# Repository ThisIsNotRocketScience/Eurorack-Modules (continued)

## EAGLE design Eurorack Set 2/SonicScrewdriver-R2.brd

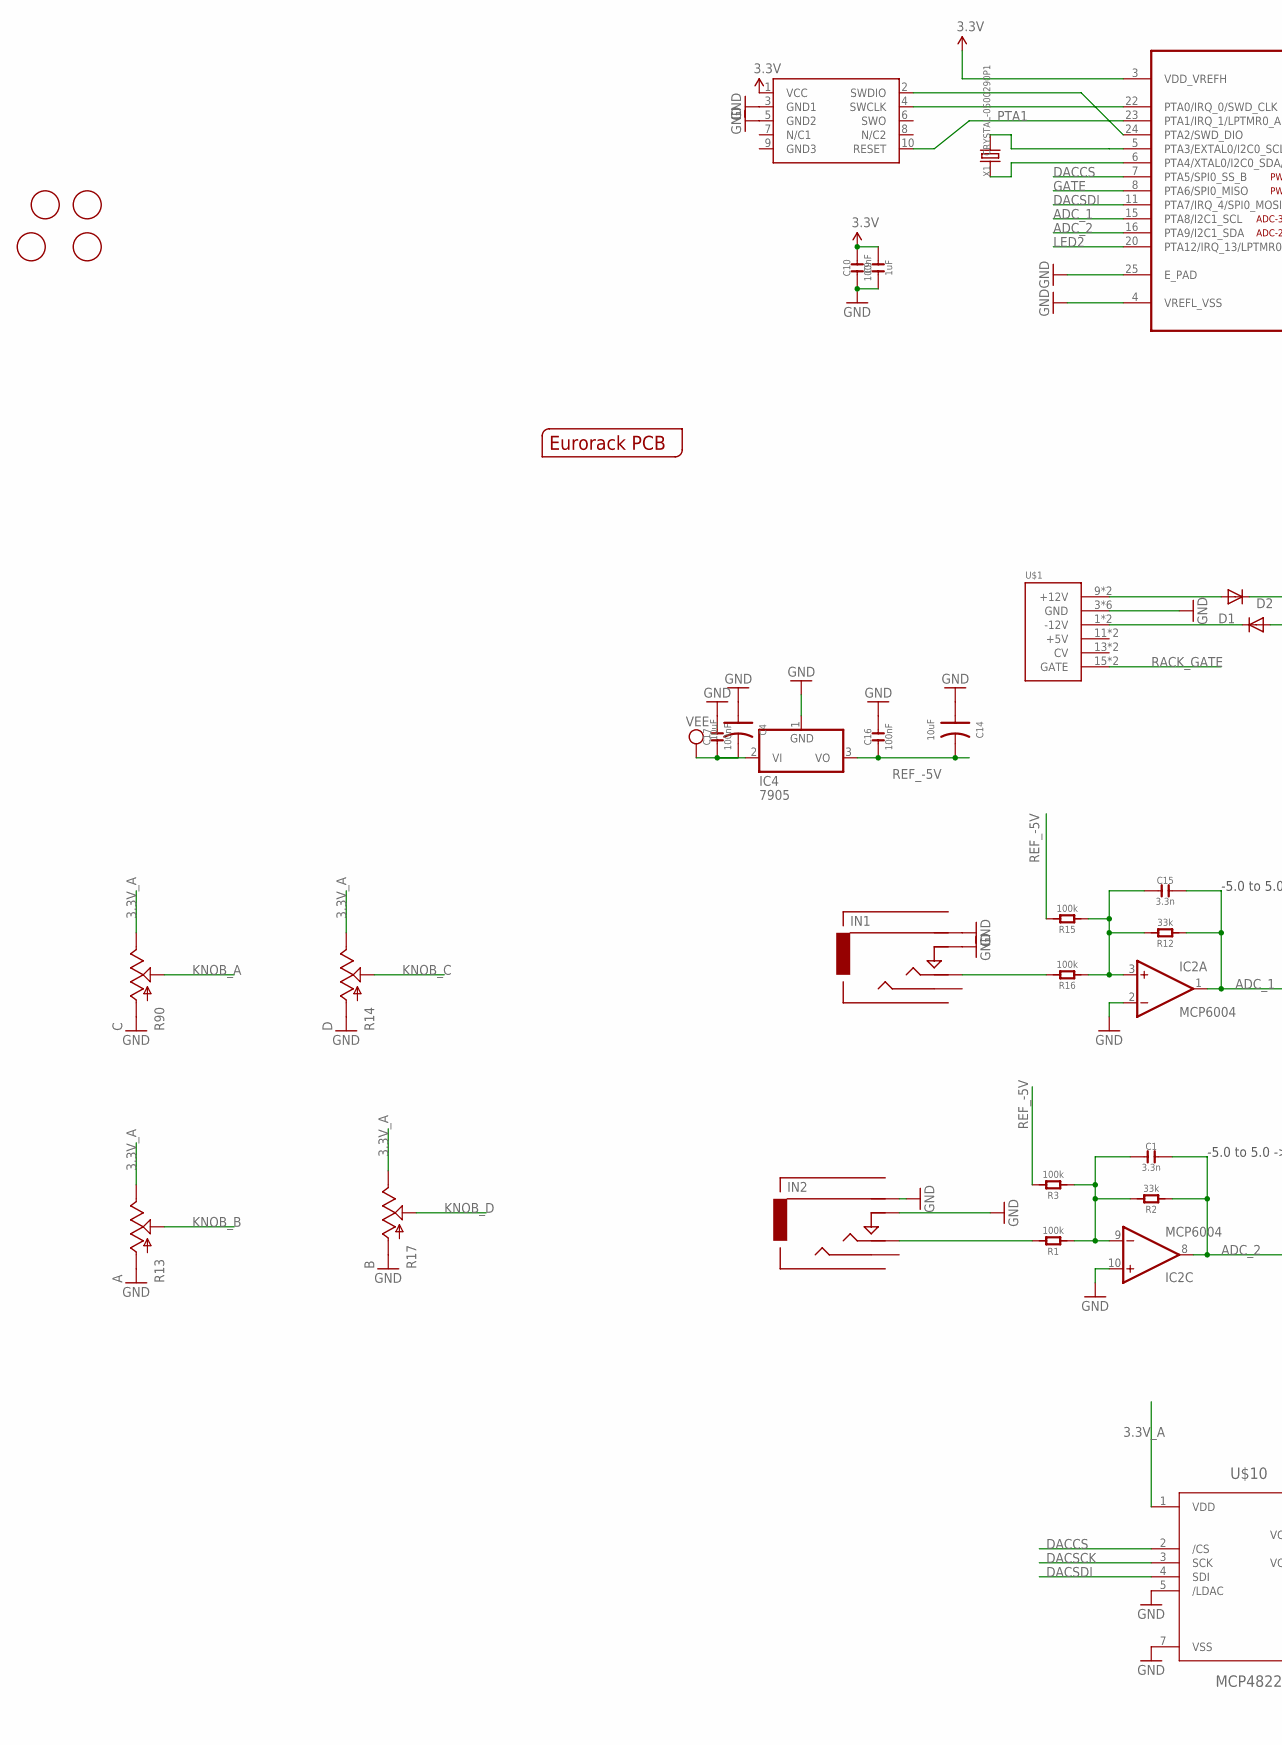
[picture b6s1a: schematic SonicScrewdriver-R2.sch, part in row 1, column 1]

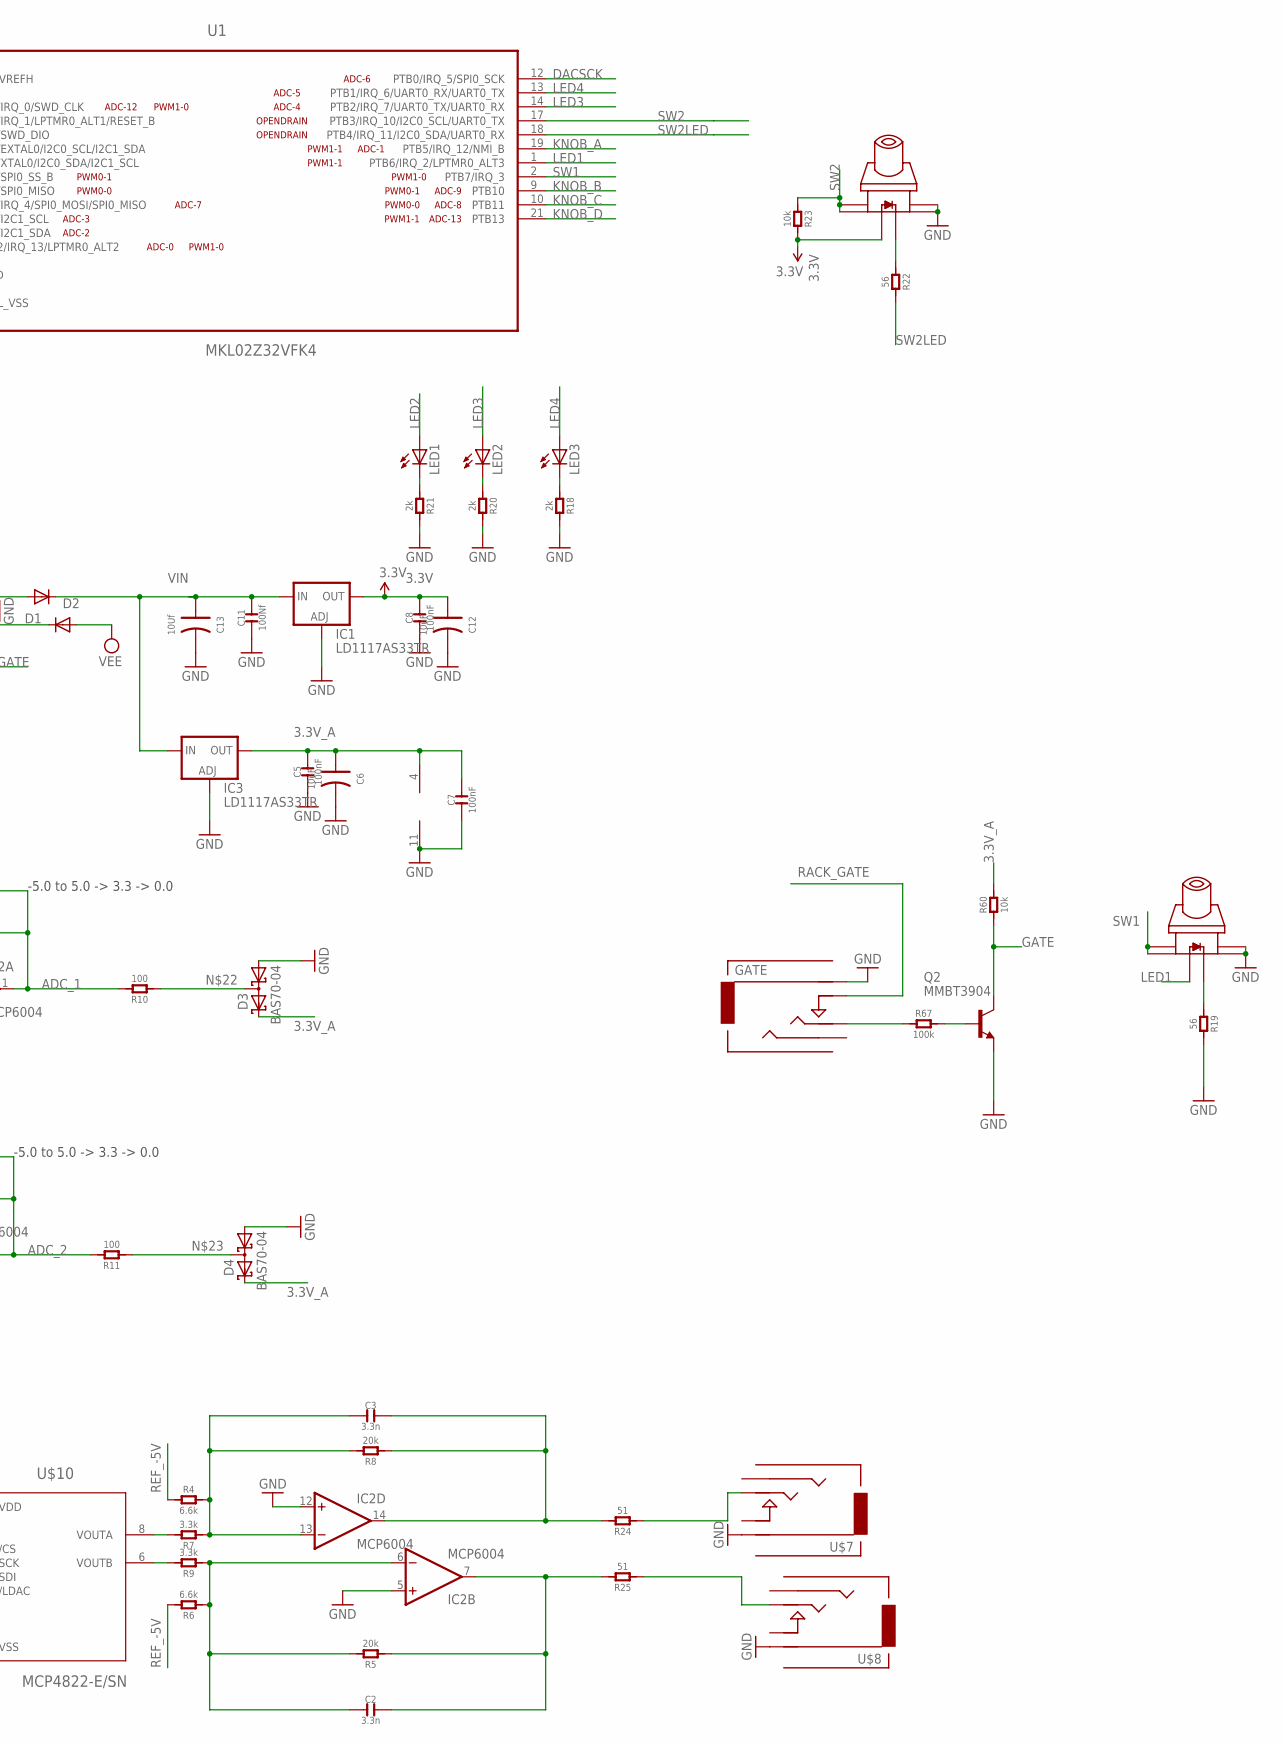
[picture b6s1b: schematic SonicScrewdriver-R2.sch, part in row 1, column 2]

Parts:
C1, C2, C3, C15: 3.3n; C0603
C4, C6, C12, C14: 10uF; AVX-A
C5, C7, C8, C10, C16, C17: 100nF; C0603
C9: 1uF; C0603
C11: 100Nf; C0603
C13: 10Uf; AVX-A
D1, D2: 1N5819HW; SOD123
D3, D4: BAS70-04; SOT23
GATE: Gate; 3.5MM-JACK-SWITCH-13MM-INPUT
IC1, IC3: LD1117AS33TR; SOT223
IC2: MCP6004; SO14
IC4: 7905; TO220H
IN1: In 2; 3.5MM-JACK-SWITCH-13MM-INPUT
IN2: In 1; 3.5MM-JACK-SWITCH-13MM-INPUT
LED1, LED2, LED3: LED3MM
Q2: MMBT3904; SOT23-BEC
R1, R3, R15, R16, R67: 100k; R0603
R2, R12: 33k; R0603
R4, R6: 6.6k; R0603
R5, R8: 20k; R0603
R7, R9: 3.3k; R0603
R10, R11: 100; R0603
R13: A; OG-POTS_ALPS_POT_VERTICAL
R14: D; OG-POTS_ALPS_POT_VERTICAL
R17: B; OG-POTS_ALPS_POT_VERTICAL
R18, R20, R21: 2k; R0603
R19, R22: 56; R0603
R23, R60: 10k; R0603
R24, R25: 51; R0603
R90: C; OG-POTS_ALPS_POT_VERTICAL
SWD1: CORTEX_SWD; M50-3600542
U1: MKL02Z32VFK4; QFN50P400X400X100-25N
U$1: POWER; POWER_16
U$2: EURORACK_PCB8HP; EURORACK8HPPCB
U$3, U$6: SWITCH_W_LED_PB6149L-X-102WHITE; PB6149L
U$4, U$5, U$9, U$11: FIDUCIAL; FIDUCIAL_1MM
U$7: Out 2; 3.5MM-JACK-SWITCH-13MM-OUTPUT
U$8: Out 1; 3.5MM-JACK-SWITCH-13MM-OUTPUT
U$10: MCP4822-E/SN; SOIC8-N_MC
X1: CRYSTAL-0500290P1; 2P-SMD-5.0X3.2

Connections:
3.3V: C8.2, C9.2, C10.2, C12.+ (1), IC1.2 (OUT), IC1.4 (OUT), R23.2, SWD1.1 (VCC), U1.3 (VDD_VREFH), U$3.LEDPOS (POS)
3.3V_A: C5.2, C6.+ (1), C7.2, D3.2 (C2), D4.2 (C2), IC2.4 (V+), IC3.2 (OUT), IC3.4 (OUT), R13.P$1 (E), R14.P$1 (E), R17.P$1 (E), R60.2, R90.P$1 (E), U$10.1 (VDD)
ADC_1: C15.2, IC2.1 (OUT), R10.2, R12.1, U1.15 (PTA8/I2C1_SCL)
ADC_2: C1.2, IC2.8 (OUT), R2.1, R11.2, U1.16 (PTA9/I2C1_SDA)
DACCS: U1.7 (PTA5/SPI0_SS_B), U$10.2 (/CS)
DACSCK: U1.12 (PTB0/IRQ_5/SPI0_SCK), U$10.3 (SCK)
DACSDI: U1.11 (PTA7/IRQ_4/SPI0_MOSI/SPI0_MISO), U$10.4 (SDI)
GATE: Q2.C, R60.1, U1.8 (PTA6/SPI0_MISO)
GND: C4.+ (1), C5.1, C6.- (2), C7.1, C8.1, C9.1, C10.1, C11.1, C12.- (2), C13.- (2), C14.+ (1), C16.2, C17.2, D3.1 (A1), D4.1 (A1), GATE.RING@1 (RING), GATE.RING@2 (RING), IC1.1 (ADJ), IC2.2 (-IN), IC2.5 (+IN), IC2.10 (+IN), IC2.11 (V-), IC2.12 (+IN), IC3.1 (ADJ), IC4.1 (GND), IN1.RING@1 (RING), IN1.RING@2 (RING), IN1.SWITCH@1 (SWITCH), IN1.SWITCH@2 (SWITCH), IN2.RING@1 (RING), IN2.RING@2 (RING), IN2.SWITCH@1 (SWITCH), IN2.SWITCH@2 (SWITCH), Q2.E, R13.P$3 (A), R14.P$3 (A), R17.P$3 (A), R18.2, R19.2, R20.2, R21.2, R90.P$3 (A), SWD1.3 (GND1), SWD1.5 (GND2), U1.4 (VREFL_VSS), U1.25 (E_PAD), U$1.3 (GND), U$1.4 (GND), U$1.5 (GND), U$1.6 (GND), U$1.7 (GND), U$1.8 (GND), U$3.3, U$3.4, U$6.3, U$6.4, U$7.RING@1 (RING), U$7.RING@2 (RING), U$8.RING@1 (RING), U$8.RING@2 (RING), U$10.5 (/LDAC), U$10.7 (VSS)
KNOB_A: R90.P$2 (S), U1.19 (PTB5/IRQ_12/NMI_B)
KNOB_B: R13.P$2 (S), U1.9 (PTB10)
KNOB_C: R14.P$2 (S), U1.10 (PTB11)
KNOB_D: R17.P$2 (S), U1.21 (PTB13)
LED1: U1.1 (PTB6/IRQ_2/LPTMR0_ALT3), U$6.LEDPOS (POS)
LED2: LED1.A, U1.20 (PTA12/IRQ_13/LPTMR0_ALT2)
LED3: LED2.A, U1.14 (PTB2/IRQ_7/UART0_TX/UART0_RX)
LED4: LED3.A, U1.13 (PTB1/IRQ_6/UART0_RX/UART0_TX)
unnamed: U1.5 (PTA3/EXTAL0/I2C0_SCL/I2C1_SDA), X1.2
unnamed: U1.6 (PTA4/XTAL0/I2C0_SDA/I2C1_SCL), X1.1
unnamed: IN1.TIP@1 (TIP), IN1.TIP@2 (TIP), R16.2
unnamed: C15.1, IC2.3 (+IN), R12.2, R15.1, R16.1
unnamed: SWD1.4 (SWCLK), U1.22 (PTA0/IRQ_0/SWD_CLK)
unnamed: IN2.TIP@1 (TIP), IN2.TIP@2 (TIP), R1.2
unnamed: SWD1.2 (SWDIO), U1.24 (PTA2/SWD_DIO)
unnamed: C1.1, IC2.9 (-IN), R1.1, R2.2, R3.1
unnamed: C2.1, IC2.6 (-IN), R5.2, R6.1, R9.1
unnamed: C3.1, IC2.13 (-IN), R4.2, R7.1, R8.2
unnamed: R7.2, U$10.8 (VOUTA)
unnamed: R9.2, U$10.6 (VOUTB)
unnamed: D1.A, U$1.9 (+12V), U$1.10 (+12V)
unnamed: R19.1, U$6.LEDNEG (NEG)
unnamed: LED3.K (C), R18.1
unnamed: LED2.K (C), R20.1
unnamed: LED1.K (C), R21.1
unnamed: C3.2, IC2.14 (OUT), R8.1, R24.2
unnamed: R22.1, U$3.LEDNEG (NEG)
unnamed: R25.1, U$8.TIP@1 (TIP), U$8.TIP@2 (TIP)
unnamed: R24.1, U$7.TIP@1 (TIP), U$7.TIP@2 (TIP)
unnamed: D3.3 (C1A2), R10.1
unnamed: D4.3 (C1A2), R11.1
unnamed: C2.2, IC2.7 (OUT), R5.1, R25.2
unnamed: GATE.TIP@1 (TIP), GATE.TIP@2 (TIP), R67.1
unnamed: D2.C, U$1.1 (-12V), U$1.2 (-12V)
unnamed: Q2.B, R67.2
PTA1: SWD1.10 (RESET), U1.23 (PTA1/IRQ_1/LPTMR0_ALT1/RESET_B)
RACK_GATE: GATE.SWITCH@1 (SWITCH), GATE.SWITCH@2 (SWITCH), U$1.15 (GATE), U$1.16 (GATE)
REF_-5V: C14.- (2), C16.1, IC4.3 (VO), R3.2, R4.1, R6.2, R15.2
SW1: U1.2 (PTB7/IRQ_3), U$6.1, U$6.2
SW2: R23.1, U1.17 (PTB3/IRQ_10/I2C0_SCL/UART0_TX), U$3.1, U$3.2
SW2LED: R22.2, U1.18 (PTB4/IRQ_11/I2C0_SDA/UART0_RX)
VEE: C4.- (2), C17.1, D2.A, IC4.2 (VI)
VIN: C11.2, C13.+ (1), D1.C, IC1.3 (IN), IC3.3 (IN)

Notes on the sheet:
-5.0 to 5.0 -> 3.3 -> 0.0

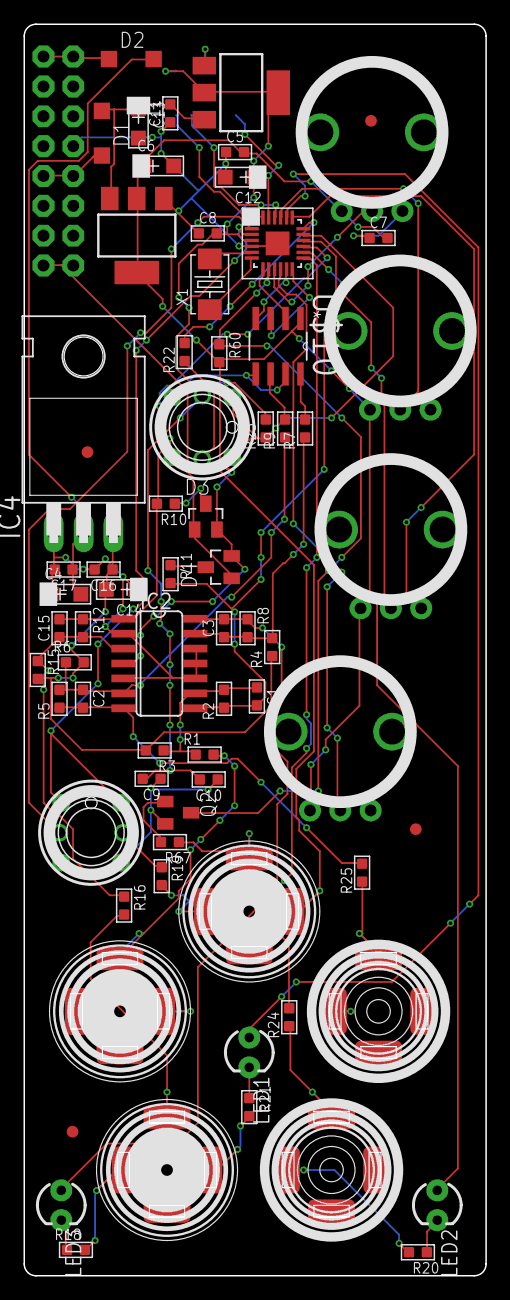
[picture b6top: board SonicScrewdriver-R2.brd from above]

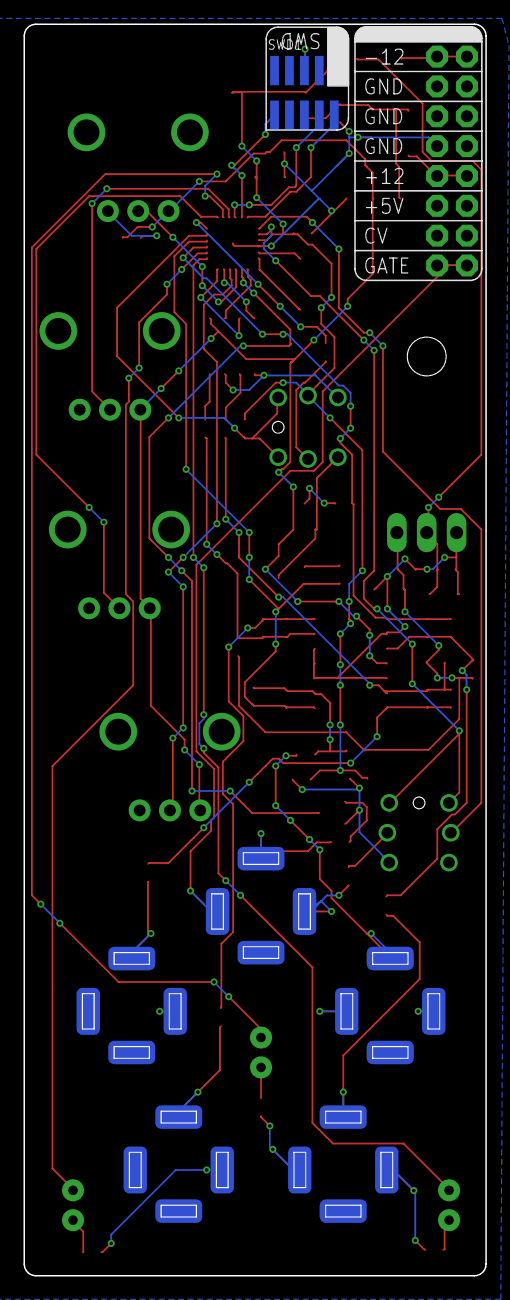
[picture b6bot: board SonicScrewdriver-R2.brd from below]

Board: 2 copper layers, 39.3 x 106.5 mm, 74 parts (2 on the bottom side), 52 nets.

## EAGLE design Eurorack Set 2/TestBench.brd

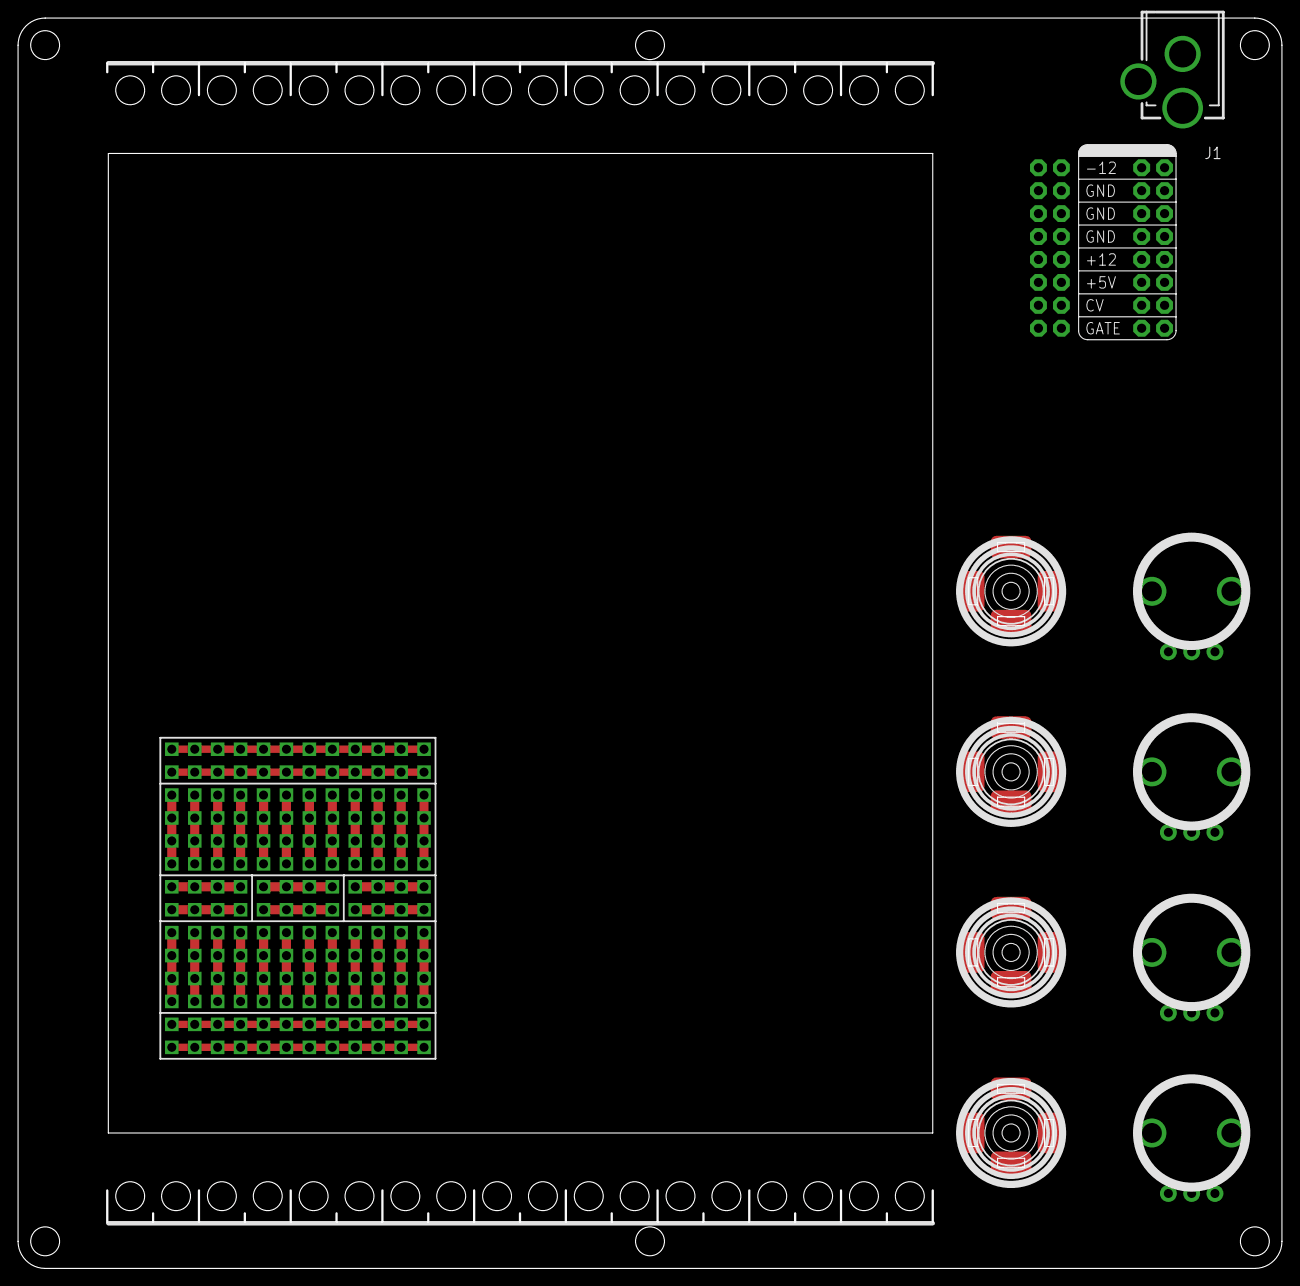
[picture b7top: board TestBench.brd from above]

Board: 2 copper layers, 140.0 x 138.5 mm, 12 parts (1 on the bottom side), 6 nets, no tracks yet.

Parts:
J1: DC_BARREL_JACK_PTH_2MM
U$1, U$2: POWER; POWER_16
U$3: PROTOAREA; PROTO_10_24
U$4, U$5, U$6, U$7: OG-POTS_ALPS_POT_VERTICAL
U$8, U$9, U$10, U$11: AUDIO-JACKOUTPUT; 3.5MM-JACK-SWITCH-13MM-OUTPUT

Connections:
unnamed: U$1.9, U$1.10, U$2.9, U$2.10
unnamed: U$1.3, U$1.4, U$1.5, U$1.6, U$1.7, U$1.8, U$2.3, U$2.4, U$2.5, U$2.6, U$2.7, U$2.8
unnamed: U$1.1, U$1.2, U$2.1, U$2.2
unnamed: U$1.11, U$1.12, U$2.11, U$2.12
unnamed: U$1.13, U$1.14, U$2.13, U$2.14
unnamed: U$1.15, U$1.16, U$2.15, U$2.16

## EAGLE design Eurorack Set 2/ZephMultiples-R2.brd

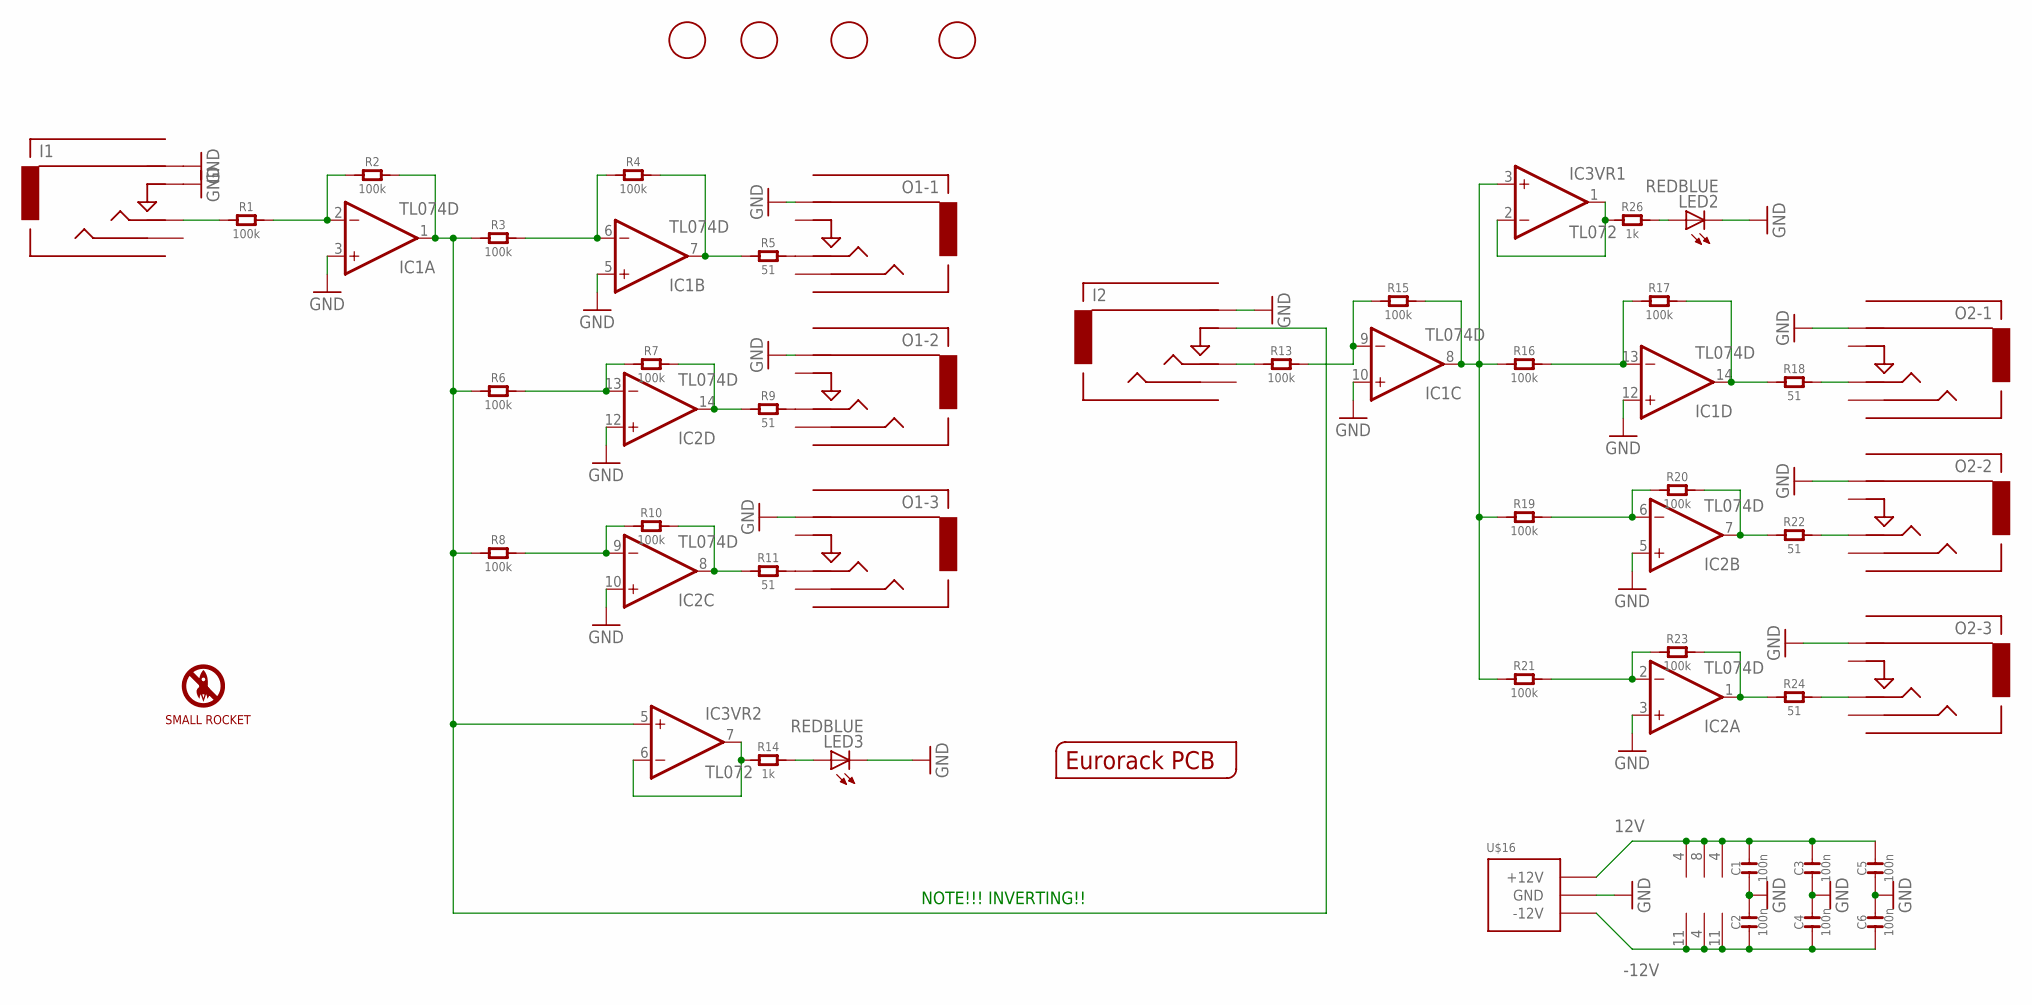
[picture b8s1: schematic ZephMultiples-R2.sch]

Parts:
C1, C2, C3, C4, C5, C6: 100n; C0603
I1: In 1; 3.5MM-JACK-SWITCH-13MM-INPUT
I2: In 2; 3.5MM-JACK-SWITCH-13MM-INPUT
IC1, IC2: TL074D; SO14
IC3: TL072; SO08
LED2, LED3: REDBLUE; LED3MM
O1-1, O1-2, O1-3, O2-1, O2-2, O2-3: AUDIO-JACKOUTPUT; 3.5MM-JACK-SWITCH-13MM-OUTPUT
R1, R2, R3, R4, R6, R7, R8, R10, R13, R15, R16, R17, R19, R20, R21, R23: 100k; R0603
R5, R9, R11, R18, R22, R24: 51; R0603
R14, R26: 1k; R0603
U$1: SMALLROCKET
U$2, U$3, U$4, U$5: FIDUCIAL; FIDUCIAL_1MM
U$15: EURORACK_PCB4HP; EURORACK4HPPCB
U$16: POWER_SIMPLE10-OTHERSIDE; POWER_10_LABELSOTHERSIDE

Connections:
12V: C1.2, C3.2, C5.2, IC1.4 (V+), IC2.4 (V+), IC3.8 (V+), U$16.9 (+12V), U$16.10 (+12V)
-12V: C2.1, C4.1, C6.1, IC1.11 (V-), IC2.11 (V-), IC3.4 (V-), U$16.1 (-12V), U$16.2 (-12V)
GND: C1.1, C2.2, C3.1, C4.2, C5.1, C6.2, I1.RING@1 (RING), I1.RING@2 (RING), I1.SWITCH@1 (SWITCH), I1.SWITCH@2 (SWITCH), I2.RING@1 (RING), I2.RING@2 (RING), IC1.3 (+IN), IC1.5 (+IN), IC1.10 (+IN), IC1.12 (+IN), IC2.3 (+IN), IC2.5 (+IN), IC2.10 (+IN), IC2.12 (+IN), LED2.K (C), LED3.K (C), O1-1.RING@1 (RING), O1-1.RING@2 (RING), O1-2.RING@1 (RING), O1-2.RING@2 (RING), O1-3.RING@1 (RING), O1-3.RING@2 (RING), O2-1.RING@1 (RING), O2-1.RING@2 (RING), O2-2.RING@1 (RING), O2-2.RING@2 (RING), O2-3.RING@1 (RING), O2-3.RING@2 (RING), U$16.3 (GND), U$16.4 (GND), U$16.5 (GND), U$16.6 (GND), U$16.7 (GND), U$16.8 (GND)
LED2DRIVE: IC3.6 (-IN), IC3.7 (OUT), R14.1
LED3DRIVE: IC3.1 (OUT), IC3.2 (-IN), R26.1
unnamed: I1.TIP@1 (TIP), I1.TIP@2 (TIP), R1.1
unnamed: IC1.2 (-IN), R1.2, R2.1
unnamed: I2.SWITCH@1 (SWITCH), I2.SWITCH@2 (SWITCH), IC1.1 (OUT), IC3.5 (+IN), R2.2, R3.1, R6.1, R8.1
unnamed: IC1.6 (-IN), R3.2, R4.1
unnamed: IC1.7 (OUT), R4.2, R5.1
unnamed: IC2.13 (-IN), R6.2, R7.1
unnamed: IC2.9 (-IN), R8.2, R10.1
unnamed: IC2.14 (OUT), R7.2, R9.1
unnamed: IC2.8 (OUT), R10.2, R11.1
unnamed: LED3.A, R14.2
unnamed: O1-1.TIP@1 (TIP), O1-1.TIP@2 (TIP), R5.2
unnamed: O1-2.TIP@1 (TIP), O1-2.TIP@2 (TIP), R9.2
unnamed: O1-3.TIP@1 (TIP), O1-3.TIP@2 (TIP), R11.2
unnamed: I2.TIP@1 (TIP), I2.TIP@2 (TIP), R13.1
unnamed: IC1.9 (-IN), R13.2, R15.1
unnamed: IC1.8 (OUT), IC3.3 (+IN), R15.2, R16.1, R19.1, R21.1
unnamed: IC1.13 (-IN), R16.2, R17.1
unnamed: IC1.14 (OUT), R17.2, R18.1
unnamed: IC2.6 (-IN), R19.2, R20.1
unnamed: IC2.2 (-IN), R21.2, R23.1
unnamed: IC2.7 (OUT), R20.2, R22.1
unnamed: IC2.1 (OUT), R23.2, R24.1
unnamed: LED2.A, R26.2
unnamed: O2-1.TIP@1 (TIP), O2-1.TIP@2 (TIP), R18.2
unnamed: O2-2.TIP@1 (TIP), O2-2.TIP@2 (TIP), R22.2
unnamed: O2-3.TIP@1 (TIP), O2-3.TIP@2 (TIP), R24.2

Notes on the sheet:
NOTE!!! INVERTING!!

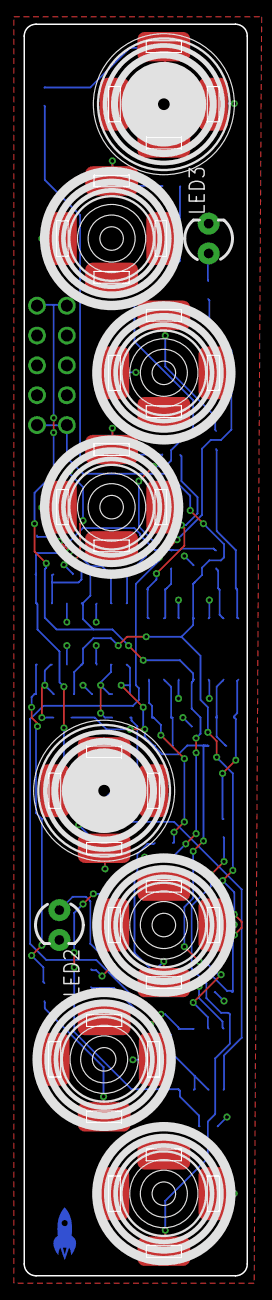
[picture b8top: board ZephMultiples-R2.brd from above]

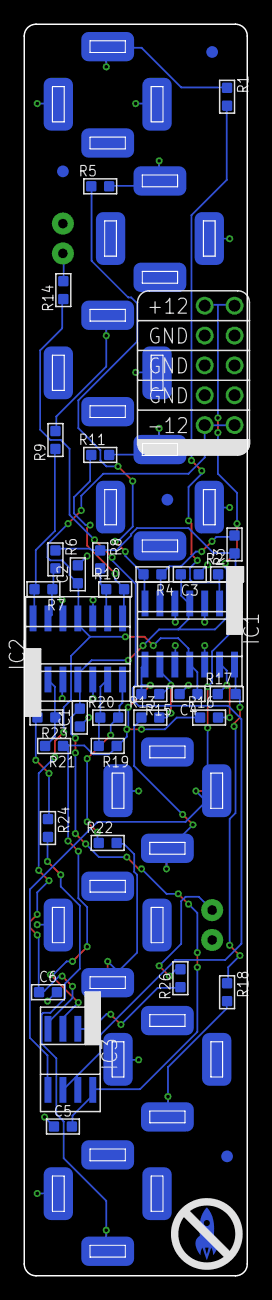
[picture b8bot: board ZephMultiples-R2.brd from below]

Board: 2 copper layers, 19.0 x 106.5 mm, 50 parts (39 on the bottom side), 31 nets.
